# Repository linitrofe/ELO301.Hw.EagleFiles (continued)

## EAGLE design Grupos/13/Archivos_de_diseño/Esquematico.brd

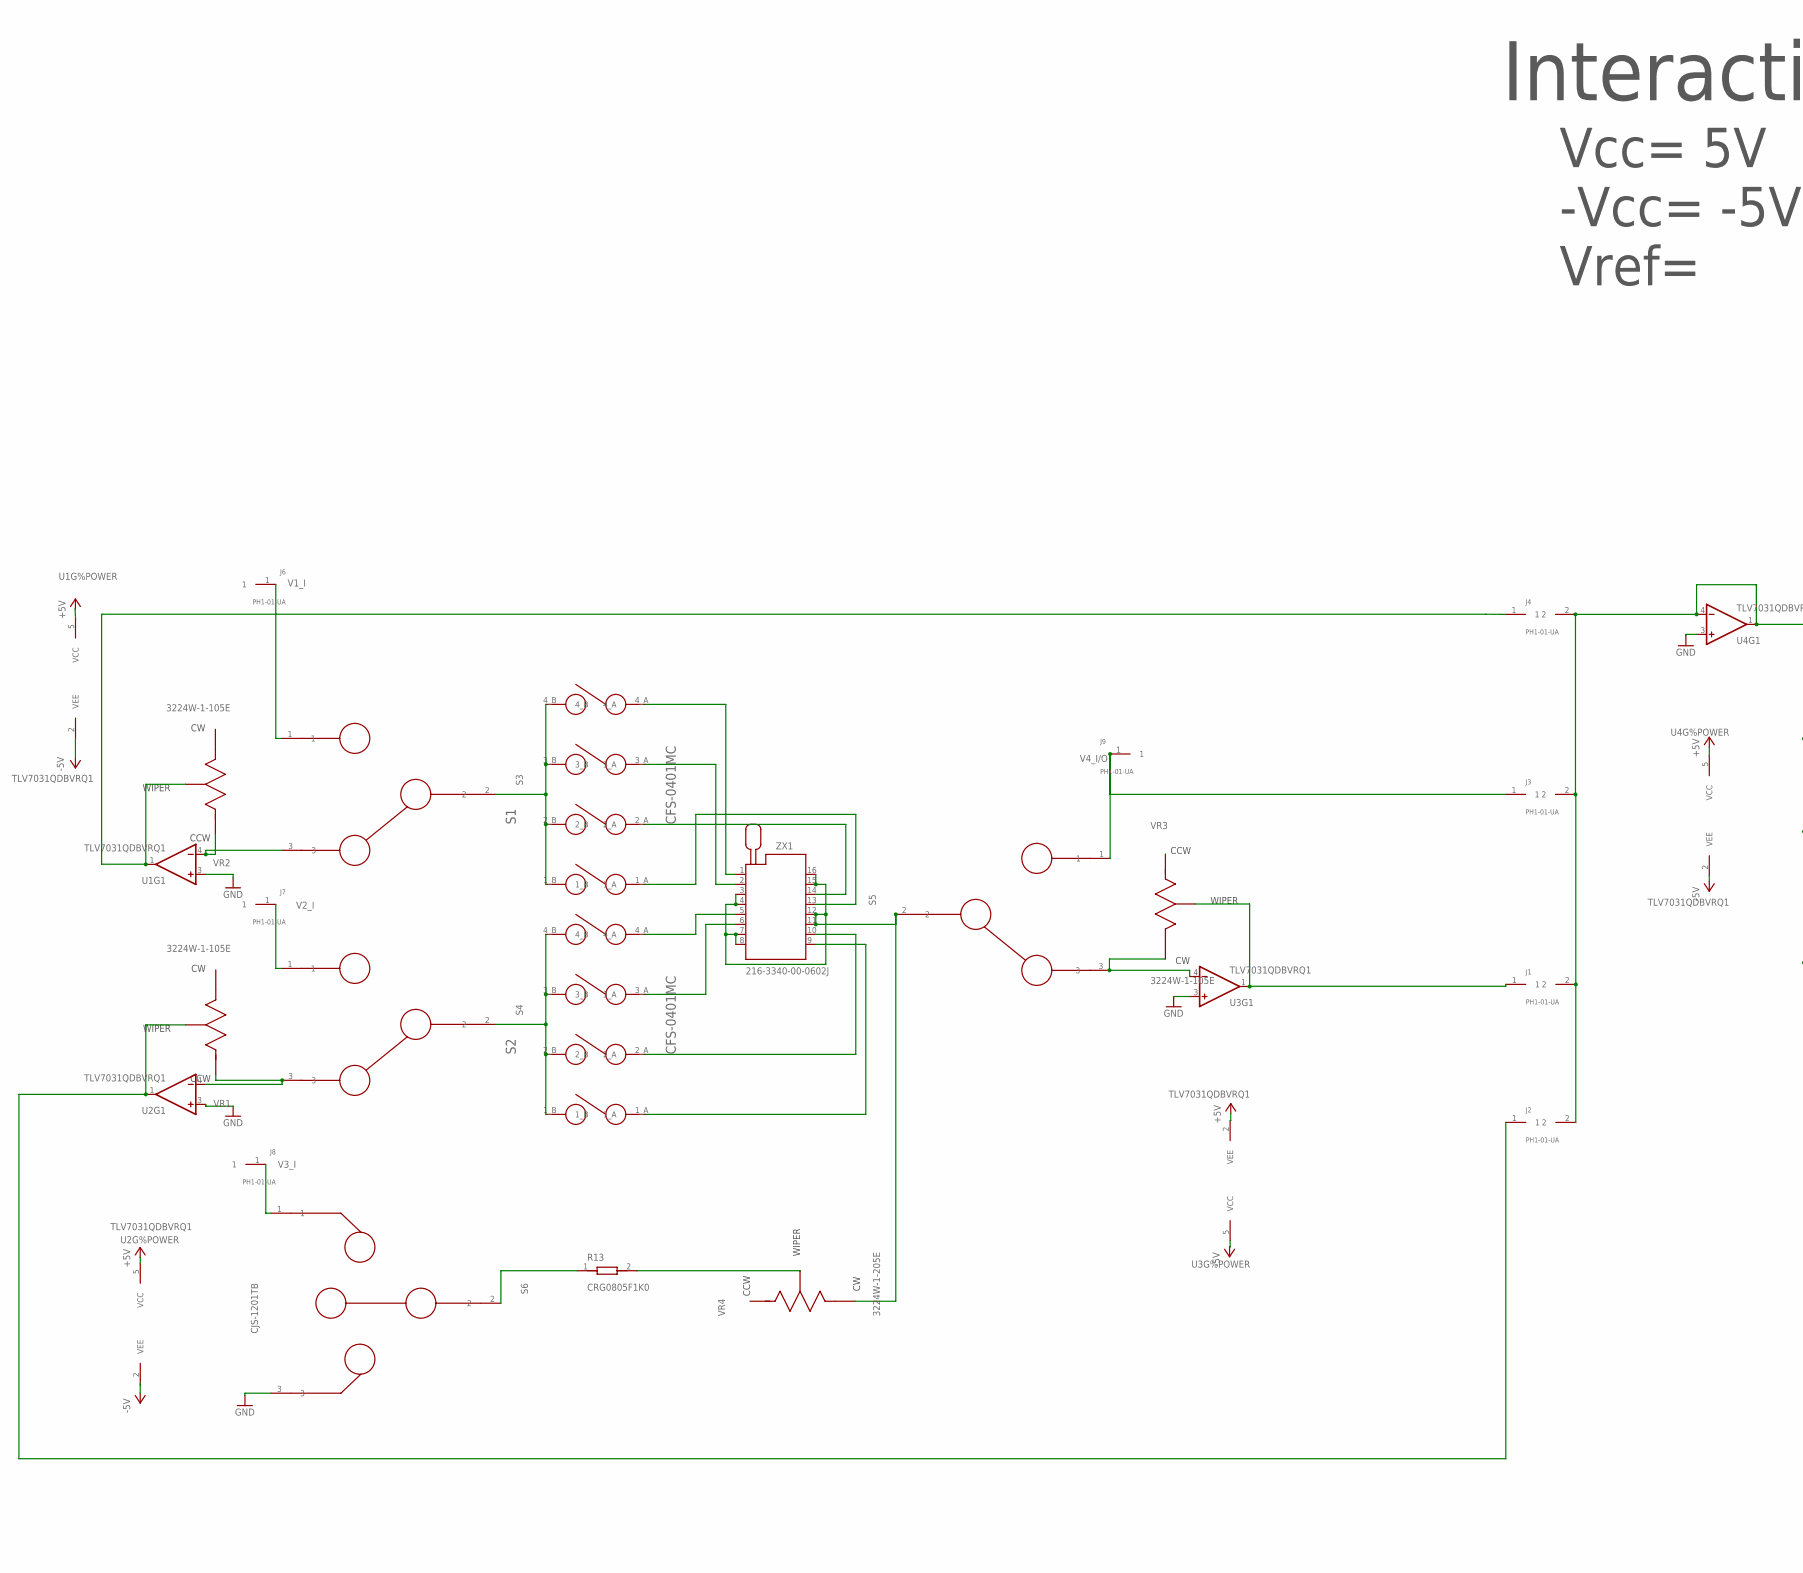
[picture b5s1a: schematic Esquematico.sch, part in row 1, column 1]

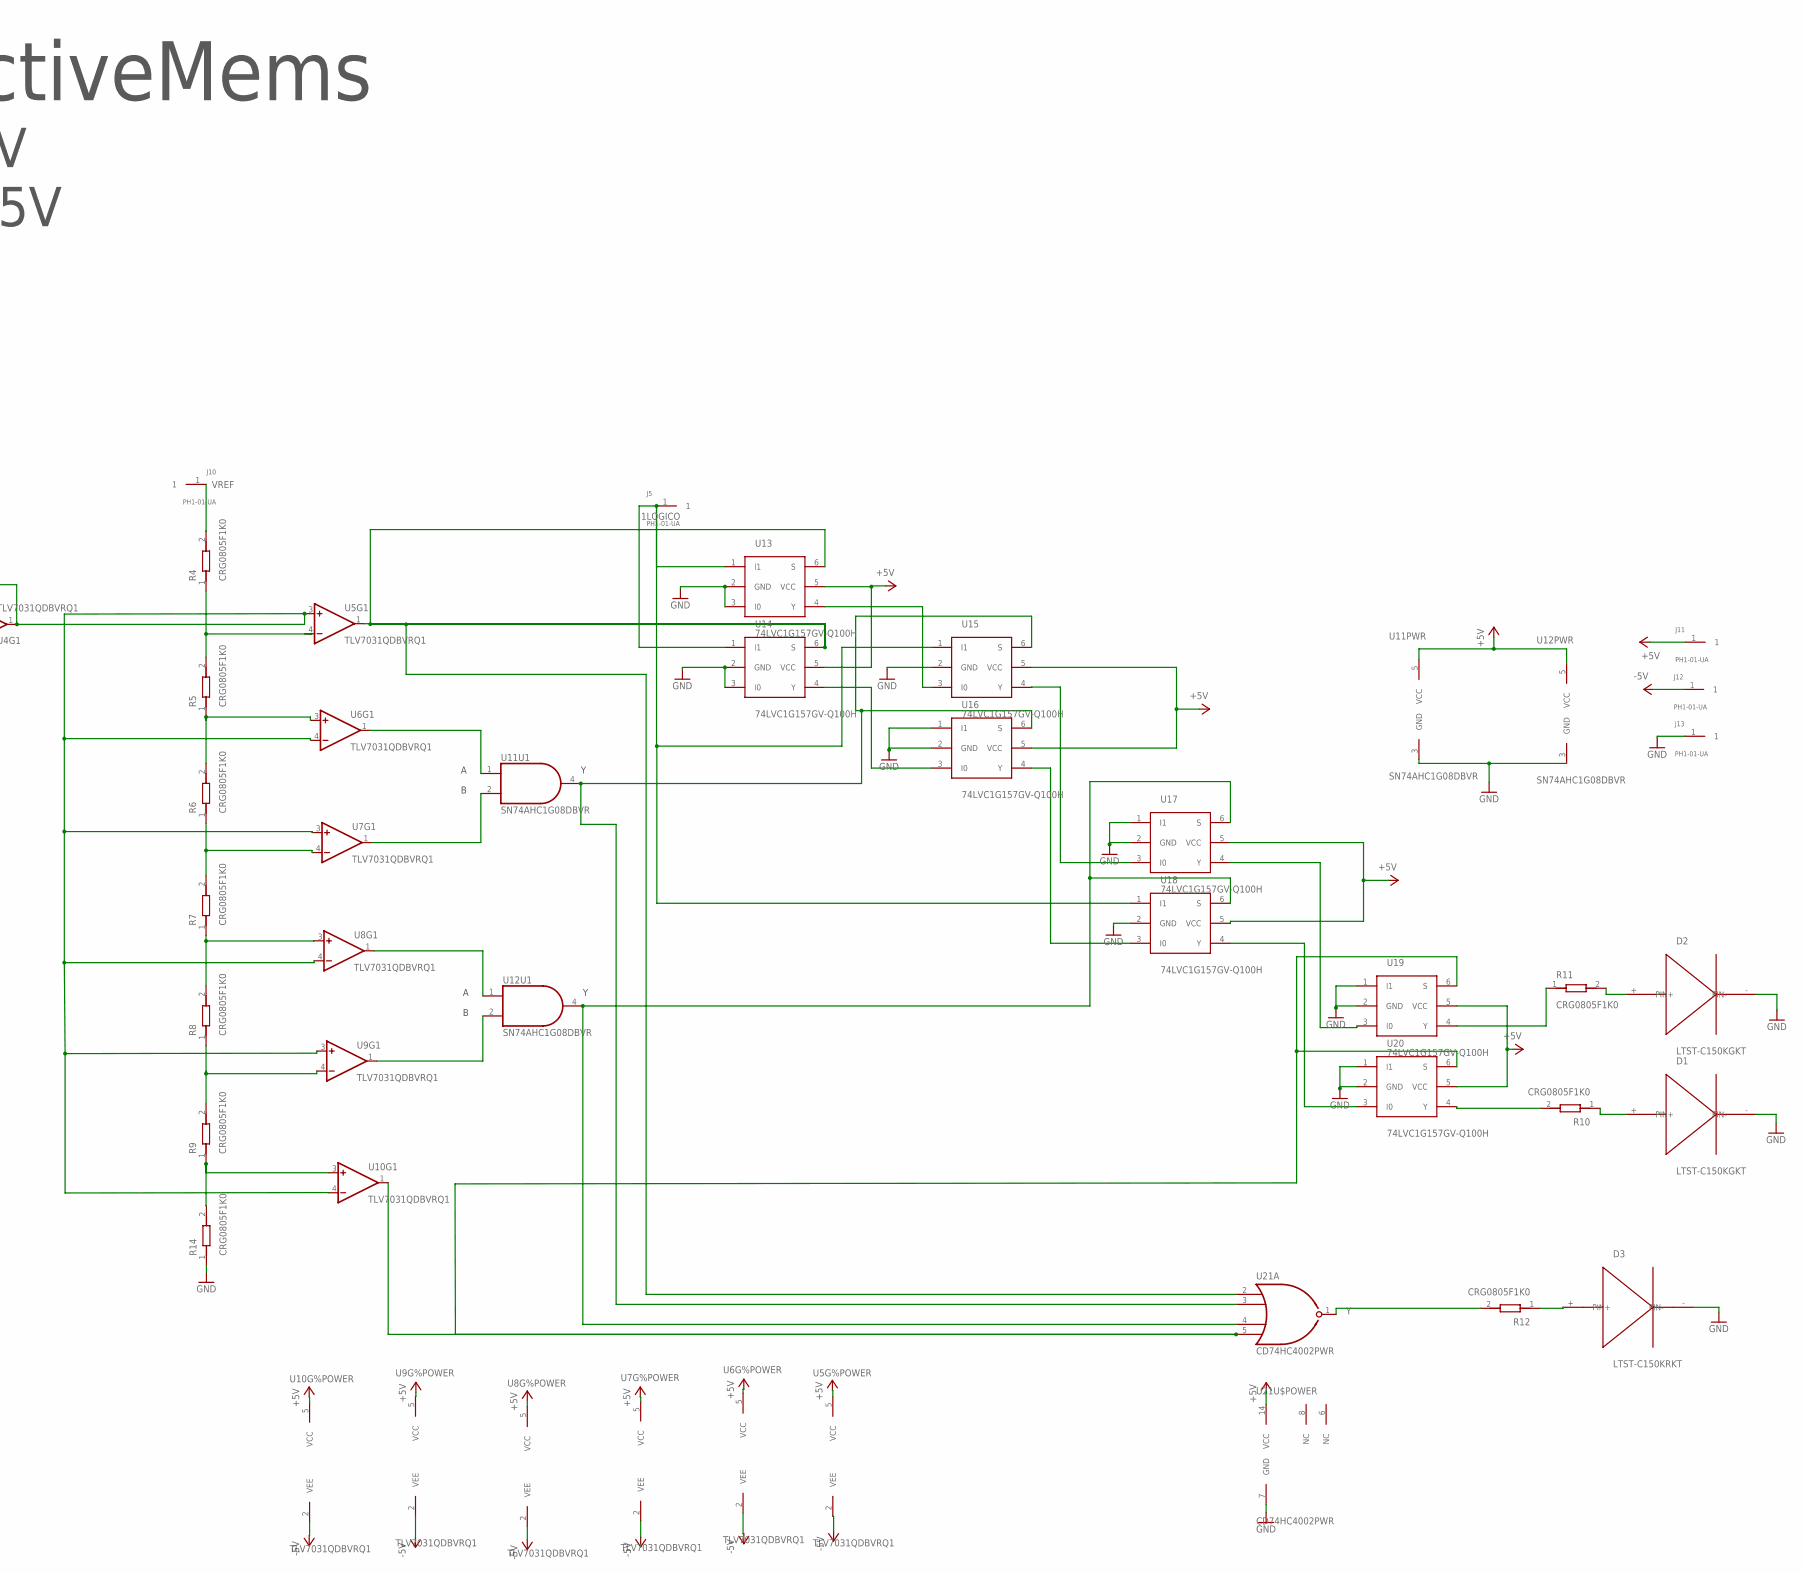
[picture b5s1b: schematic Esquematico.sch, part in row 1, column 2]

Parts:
D1, D2: LTST-C150KGKT; 1206; PARTNO LTST-C150KGKT
D3: LTST-C150KRKT; 1206; PARTNO LTST-C150KRKT
J1, J2, J3, J4, J5, J6, J7, J8, J9, J10, J11, J12, J13: PH1-01-UA; HEADER; PARTNO PH1-01-UA
R4, R5, R6, R7, R8, R9, R10, R11, R12, R13, R14: CRG0805F1K0; 0805; PARTNO CRG0805F1K0
S1, S2: CFS-0401MC; DIP_SPST-4; PARTNO CFS-0401MC
S3, S4, S5: CJS-1200TB; SPDT; PARTNO CJS-1200TB
S6: CJS-1201TB; SPDT_ON-OFF-ON; PARTNO CJS-1201TB
U1, U2, U3, U4, U5, U6, U7, U8, U9, U10: TLV7031QDBVRQ1; SOT-23; PARTNO TLV7031QDBVRQ1
U11, U12: SN74AHC1G08DBVR; SOT-23-5; PARTNO SN74AHC1G08DBVR
U13, U14, U15, U16, U17, U18, U19, U20: 74LVC1G157GV-Q100H; 6-TSOP; PARTNO 74LVC1G157GV-Q100H
U21: CD74HC4002PWR; 14-TSSOP; PARTNO CD74HC4002PWR
VR1, VR2, VR3: 3224W-1-105E; 3224W-1-205E; PARTNO 3224W-1-105E
VR4: 3224W-1-205E; PARTNO 3224W-1-205E
ZX1: 216-3340-00-0602J; PARTNO 216-3340-00-0602J

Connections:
1LOGICO: J5.1, U13.1 (I1), U14.1 (I1), U15.1 (I1), U18.1 (I1)
+5V: J11.1, U1.5 (VCC), U2.5 (VCC), U3.2 (VEE), U4.5 (VCC), U5.5 (VCC), U6.5 (VCC), U7.5 (VCC), U8.5 (VCC), U9.5 (VCC), U10.5 (VCC), U11.5 (VCC), U12.5 (VCC), U13.5 (VCC), U14.5 (VCC), U15.5 (VCC), U16.5 (VCC), U17.5 (VCC), U18.5 (VCC), U19.5 (VCC), U20.5 (VCC), U21.14 (VCC)
-5V: J12.1, U1.2 (VEE), U2.2 (VEE), U3.5 (VCC), U4.2 (VEE), U5.2 (VEE), U6.2 (VEE), U7.2 (VEE), U8.2 (VEE), U9.2 (VEE), U10.2 (VEE)
GND: D1.- (PIN-), D2.- (PIN-), D3.- (PIN-), J13.1, R14.1, S6.3, U1.3 (+IN), U2.3 (+IN), U3.3 (+IN), U4.3 (+IN), U11.3 (GND), U12.3 (GND), U13.2 (GND), U13.3 (I0), U14.2 (GND), U14.3 (I0), U15.2 (GND), U16.1 (I1), U16.2 (GND), U17.1 (I1), U17.2 (GND), U18.2 (GND), U19.1 (I1), U19.2 (GND), U20.1 (I1), U20.2 (GND), U21.7 (GND)
unnamed: S5.2, VR4.3 (CW), ZX1.3, ZX1.4, ZX1.7, ZX1.8, ZX1.11, ZX1.12, ZX1.15, ZX1.16
unnamed: S1.4_A, ZX1.1
unnamed: S1.3_A, ZX1.2
unnamed: S1.2_A, ZX1.14
unnamed: S1.1_A, ZX1.13
unnamed: R6.1, R7.2, U7.4 (-IN)
unnamed: U9.1 (OUT), U12.2 (B)
unnamed: S2.2_A, ZX1.10
unnamed: S2.1_A, ZX1.9
unnamed: S1.1_B, S1.2_B, S1.3_B, S1.4_B, S3.2
unnamed: S2.1_B, S2.2_B, S2.3_B, S2.4_B, S4.2
unnamed: S3.3, U1.4 (-IN), VR2.1 (CCW)
unnamed: S4.3, U2.4 (-IN), VR1.1 (CCW)
unnamed: S5.3, U3.4 (-IN), VR3.3 (CW)
unnamed: D2.+ (PIN+), R11.2
unnamed: D1.+ (PIN+), R10.1
unnamed: D3.+ (PIN+), R12.1
unnamed: J1.2, J2.2, J3.2, J4.2, U4.1 (OUT), U4.4 (-IN), U5.3 (+IN), U6.4 (-IN), U7.3 (+IN), U8.4 (-IN), U9.3 (+IN), U10.4 (-IN)
unnamed: R13.1, S6.2
unnamed: U8.1 (OUT), U12.1 (A)
unnamed: U7.1 (OUT), U11.2 (B)
unnamed: U6.1 (OUT), U11.1 (A)
unnamed: R13.2, VR4.2 (WIPER)
unnamed: S2.4_A, ZX1.5
unnamed: R4.1, R5.2, U5.4 (-IN)
unnamed: S2.3_A, ZX1.6
unnamed: R5.1, R6.2, U6.3 (+IN)
unnamed: R9.1, R14.2, U10.3 (+IN)
unnamed: R7.1, R8.2, U8.3 (+IN)
unnamed: R8.1, R9.2, U9.4 (-IN)
unnamed: U5.1 (OUT), U13.6 (S), U14.6 (S), U21.2 (A)
unnamed: U11.4 (Y), U15.6 (S), U16.6 (S), U21.3 (B)
unnamed: U15.4 (Y), U17.3 (I0)
unnamed: U14.4 (Y), U16.3 (I0)
unnamed: U13.4 (Y), U15.3 (I0)
unnamed: U16.4 (Y), U18.3 (I0)
unnamed: U12.4 (Y), U17.6 (S), U18.6 (S), U21.4 (C)
unnamed: U17.4 (Y), U19.3 (I0)
unnamed: U18.4 (Y), U20.3 (I0)
unnamed: R10.2, U20.4 (Y)
unnamed: R11.1, U19.4 (Y)
unnamed: U10.1 (OUT), U19.6 (S), U20.6 (S), U21.5 (D)
unnamed: R12.2, U21.1 (Y)
V1_I: J6.1, S3.1
V1_O: J4.1, U1.1 (OUT), VR2.2 (WIPER)
V2_I: J7.1, S4.1
V2_O: J2.1, U2.1 (OUT), VR1.2 (WIPER)
V3_I: J8.1, S6.1
V3_O: J1.1, U3.1 (OUT), VR3.2 (WIPER)
V4_I/O: J3.1, J9.1, S5.1
VREF: J10.1, R4.2

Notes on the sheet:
InteractiveMems
Vcc= 5V -Vcc= -5V Vref=

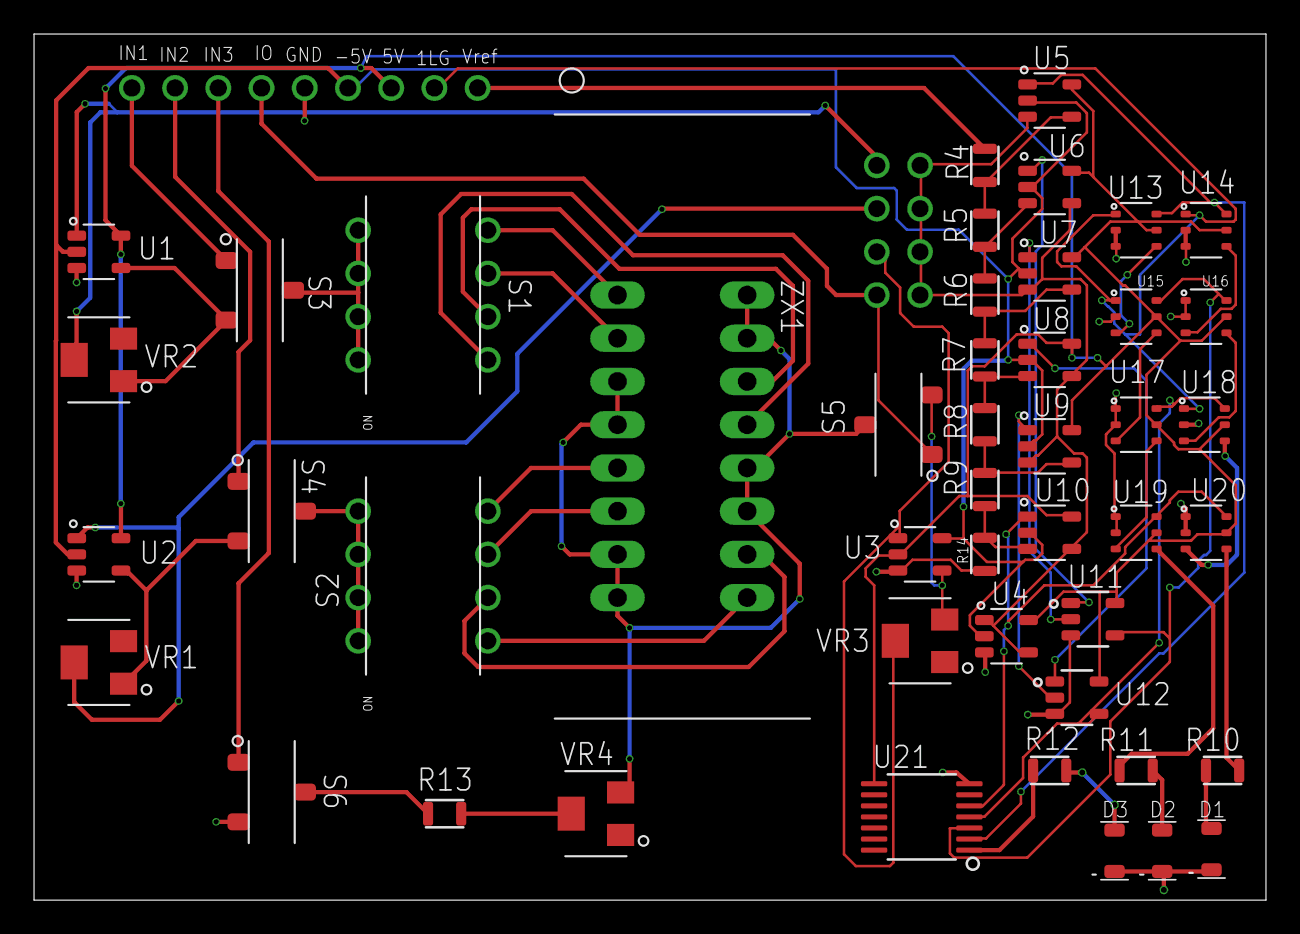
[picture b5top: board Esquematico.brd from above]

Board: 2 copper layers, 72.4 x 50.9 mm, 59 parts (0 on the bottom side), 55 nets.

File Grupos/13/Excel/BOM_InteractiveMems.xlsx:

Qty | Value | Device | Package | Parts | Description | PARTNO | Column1
1 | 216-3340-00-0602J | 216-3340-00-0602J | 216-3340-00-0602J | ZX1 | Zero Insertion Force Socked | 216-3340-00-0602J
3 | 3224W-1-105E | 3224W-1-205E | 3224W-1-205E | VR1, VR2, VR3 |  | 3224W-1-105E
1 | 3224W-1-205E | 3224W-1-205E | 3224W-1-205E | VR4 |  | 3224W-1-205E
8 | 74LVC1G157GV-Q100H | 74LVC1G157GV-Q100H | 6-TSOP | U13, U14, U15, U16, U17, U18, U19, U20 |  | 74LVC1G157GV-Q100H
1 | CD74HC4002PWR | CD74HC4002PWR | 14-TSSOP | U21 |  | CD74HC4002PWR
2 | CFS-0401MC | CFS-0401MC | DIP_SPST-4 | S1, S2 |  | CFS-0401MC
3 | CJS-1200TB | CJS-1200B | SPDT | S3, S4, S5 |  | CJS-1200TB
1 | CJS-1201TB | CJS-1201TB | SPDT_ON-OFF-ON | S6 |  | CJS-1201TB
1 | CRG0805F1K0 | CRG0805F1K0 | 0805 | R13 |  | CRG0805F1K0
10 | CRG0805F1K0 | CRG0805F1K0 | 0805 | R4, R5, R6, R7, R8, R9, R10, R11, R12, R14 |  | CRG0805F1K0
2 | LTST-C150KGKT | LTST-C150KRKT | 1206 | D1, D2 |  | LTST-C150KGKT
1 | LTST-C150KRKT | LTST-C150KRKT | 1206 | D3 |  | LTST-C150KRKT
4 | PH1-01-UA | (2X)PH1-01-UA | HEADER | J1, J2, J3, J4 |  | PH1-01-UA
6 | PH1-01-UA | PH1-01-UA | HEADER | J5, J6, J7, J8, J9, J10 |  | PH1-01-UA
3 | PH1-01-UA | PH1-01-UA | HEADER | J11, J12, J13 |  | PH1-01-UA
2 | SN74AHC1G08DBVR | SN74AHC1G08DBVR | SOT-23-5 | U11, U12 |  | SN74AHC1G08DBVR
10 | TLV7031QDBVRQ1 | TLV7031QDBVRQ1 | SOT-23 | U1, U2, U3, U4, U5, U6, U7, U8, U9, U10 |  | TLV7031QDBVRQ1

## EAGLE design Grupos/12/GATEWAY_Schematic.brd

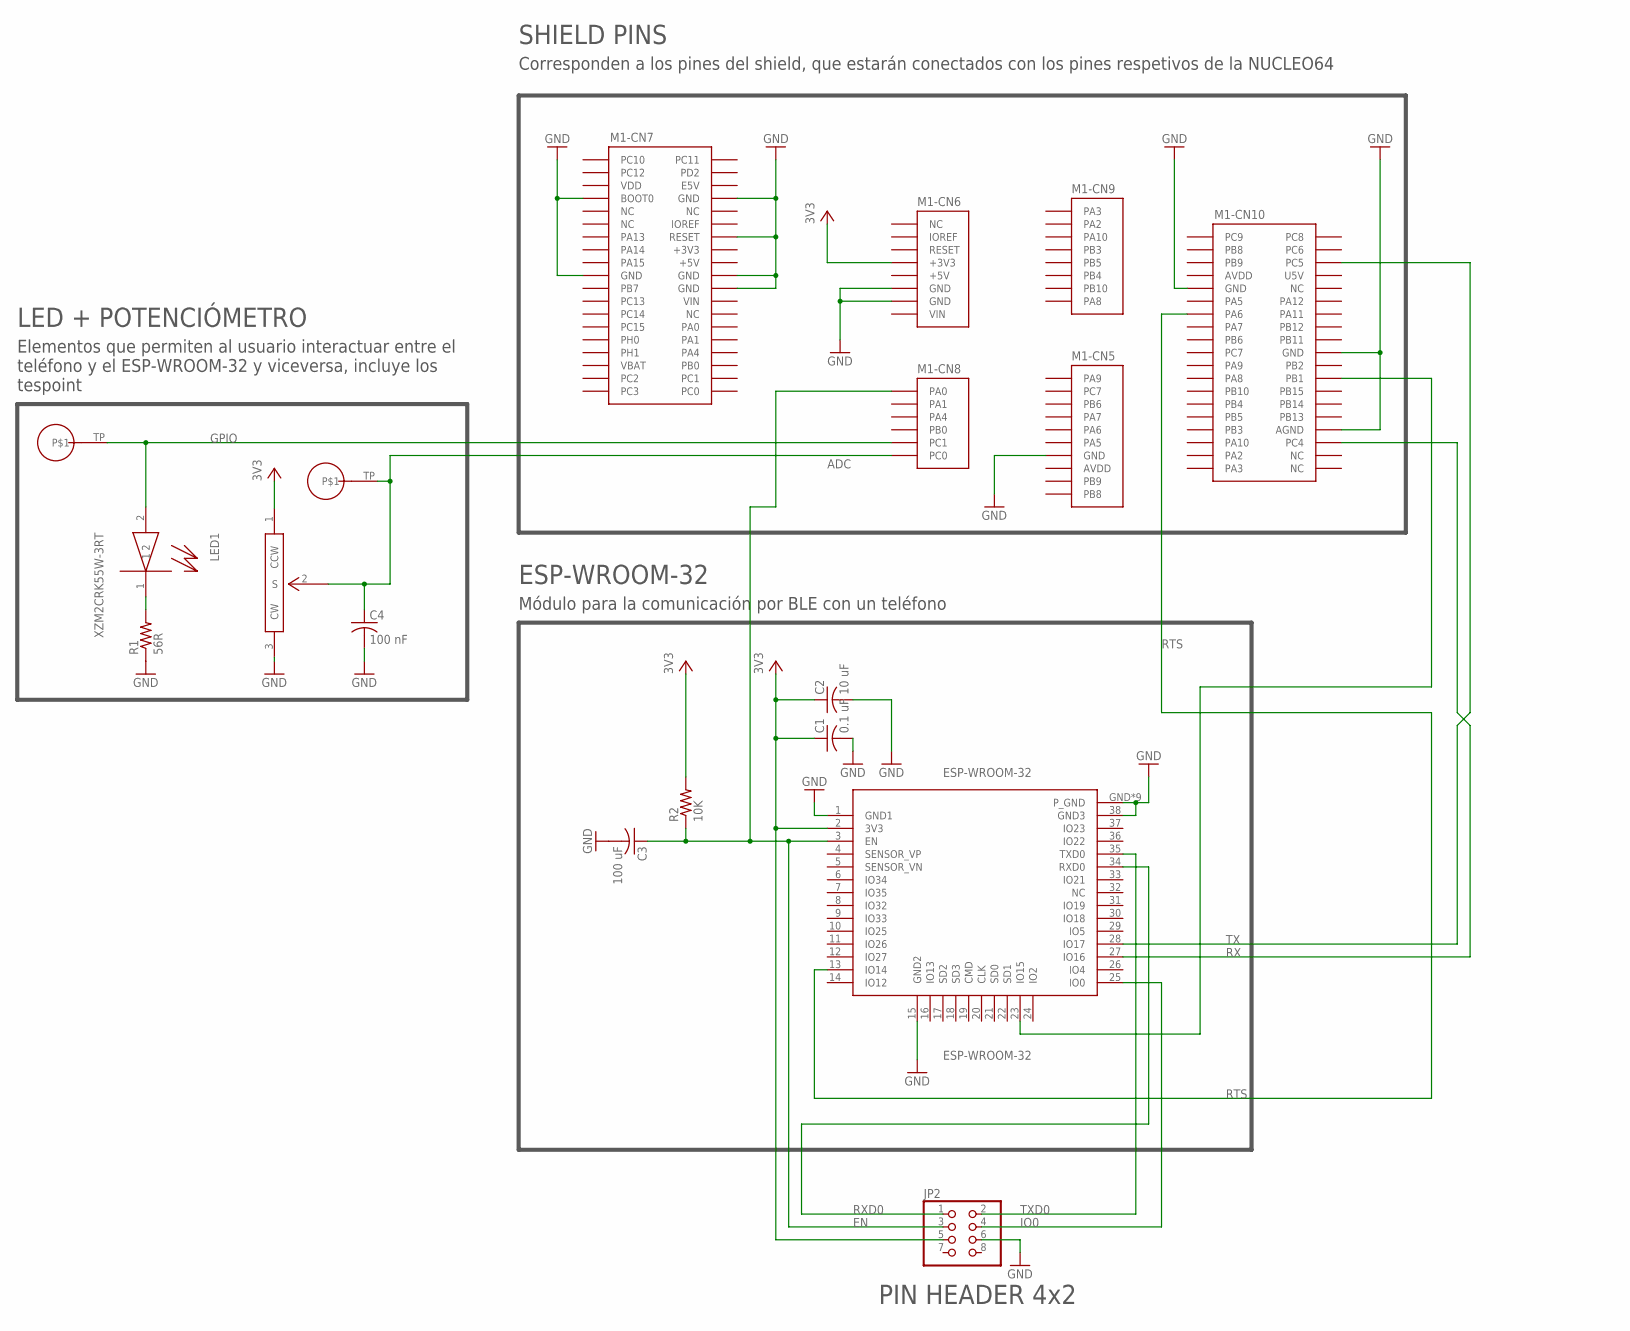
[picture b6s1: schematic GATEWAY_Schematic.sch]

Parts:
C1: 0.1 uF; C0805; PARTNO GCM21BR72A104KA37L
C2: 10 uF; C0805; PARTNO GRM21BR61C106KE15L
C3: 100 uF; C0805; PARTNO GRM21BR60J107ME15L
C4: 100 nF; C0805; PARTNO GCM21BR72A104KA37L
ESP-WROOM-32: ESP-WROOM-32; PARTNO ESP-WROOM-32
JP2: PINHD-2X4; 2X04; PARTNO 220-1-08-003
LED1: XZM2CRK55W-3RT; CHIPLED; PARTNO XZM2CRK55W-3RT
M1: NUCLEO-L452RE; NUCLEO-64; PARTNO NUCLEO-L452RE
POT1: 10K; P160KN-0QD15B10K; PARTNO P160KN-0QD15B10K
R1: 56R; R0805; PARTNO RC0805JR-0756RL
R2: 10K; R0805; PARTNO RC0805FR-0710KL
TP_LED: TP
TP_POT: TP

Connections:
+3V3: M1.CN7-16 (+3V3)
+5V: M1.CN6-5 (+5V), M1.CN7-18 (+5V)
ADC: C4.1, M1.CN8-6 (PC0), POT1.2 (S), TP_POT.TP
AVDD: M1.CN5-8 (AVDD), M1.CN10-7 (AVDD)
CTS: ESP-WROOM-32.23 (IO15), M1.CN10-24 (PB1)
EN: C3.1, ESP-WROOM-32.3 (EN), JP2.3, M1.CN8-1 (PA0), R2.1
GND: C1.2, C2.2, C3.2, C4.2, ESP-WROOM-32.1 (GND1), ESP-WROOM-32.15 (GND2), ESP-WROOM-32.38 (GND3), ESP-WROOM-32.GND (P_GND), ESP-WROOM-32.GND1 (P_GND), ESP-WROOM-32.GND2 (P_GND), ESP-WROOM-32.GND3 (P_GND), ESP-WROOM-32.GND4 (P_GND), ESP-WROOM-32.GND5 (P_GND), ESP-WROOM-32.GND6 (P_GND), ESP-WROOM-32.GND7 (P_GND), ESP-WROOM-32.GND8 (P_GND), JP2.6, M1.CN5-7 (GND), M1.CN6-6 (GND), M1.CN6-7 (GND), M1.CN7-7 (BOOT0), M1.CN7-8 (GND), M1.CN7-14 (RESET), M1.CN7-19 (GND), M1.CN7-20 (GND), M1.CN7-22 (GND), M1.CN10-9 (GND), M1.CN10-20 (GND), M1.CN10-32 (AGND), POT1.3 (CW), R1.1
GPIO: LED1.2, M1.CN8-5 (PC1), TP_LED.TP
IO0: ESP-WROOM-32.25 (IO0), JP2.4
IOREF: M1.CN6-2 (IOREF)
unnamed: LED1.1, R1.2
RTS: ESP-WROOM-32.13 (IO14), M1.CN10-13 (PA6)
RX: ESP-WROOM-32.27 (IO16), M1.CN10-34 (PC4)
RXD0: ESP-WROOM-32.34 (RXD0), JP2.1
TX: ESP-WROOM-32.28 (IO17), M1.CN10-6 (PC5)
TXD0: ESP-WROOM-32.35 (TXD0), JP2.2
U5V: M1.CN10-8 (U5V)
VBAT: M1.CN7-33 (VBAT)
VCC: C1.1, C2.1, ESP-WROOM-32.2 (3V3), JP2.5, M1.CN6-4 (+3V3), POT1.1 (CCW), R2.2
VDD: M1.CN7-5 (VDD)
VIN: M1.CN6-8 (VIN), M1.CN7-24 (VIN)

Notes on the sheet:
LED + POTENCIÓMETRO
SHIELD PINS
ESP-WROOM-32
PIN HEADER 4x2
Corresponden a los pines del shield, que estarán conectados con los pines respetivos de la NUCLEO64
Elementos que permiten al usuario interactuar entre el teléfono y el ESP-WROOM-32 y viceversa, incluye los tespoint
Módulo para la comunicación por BLE con un teléfono

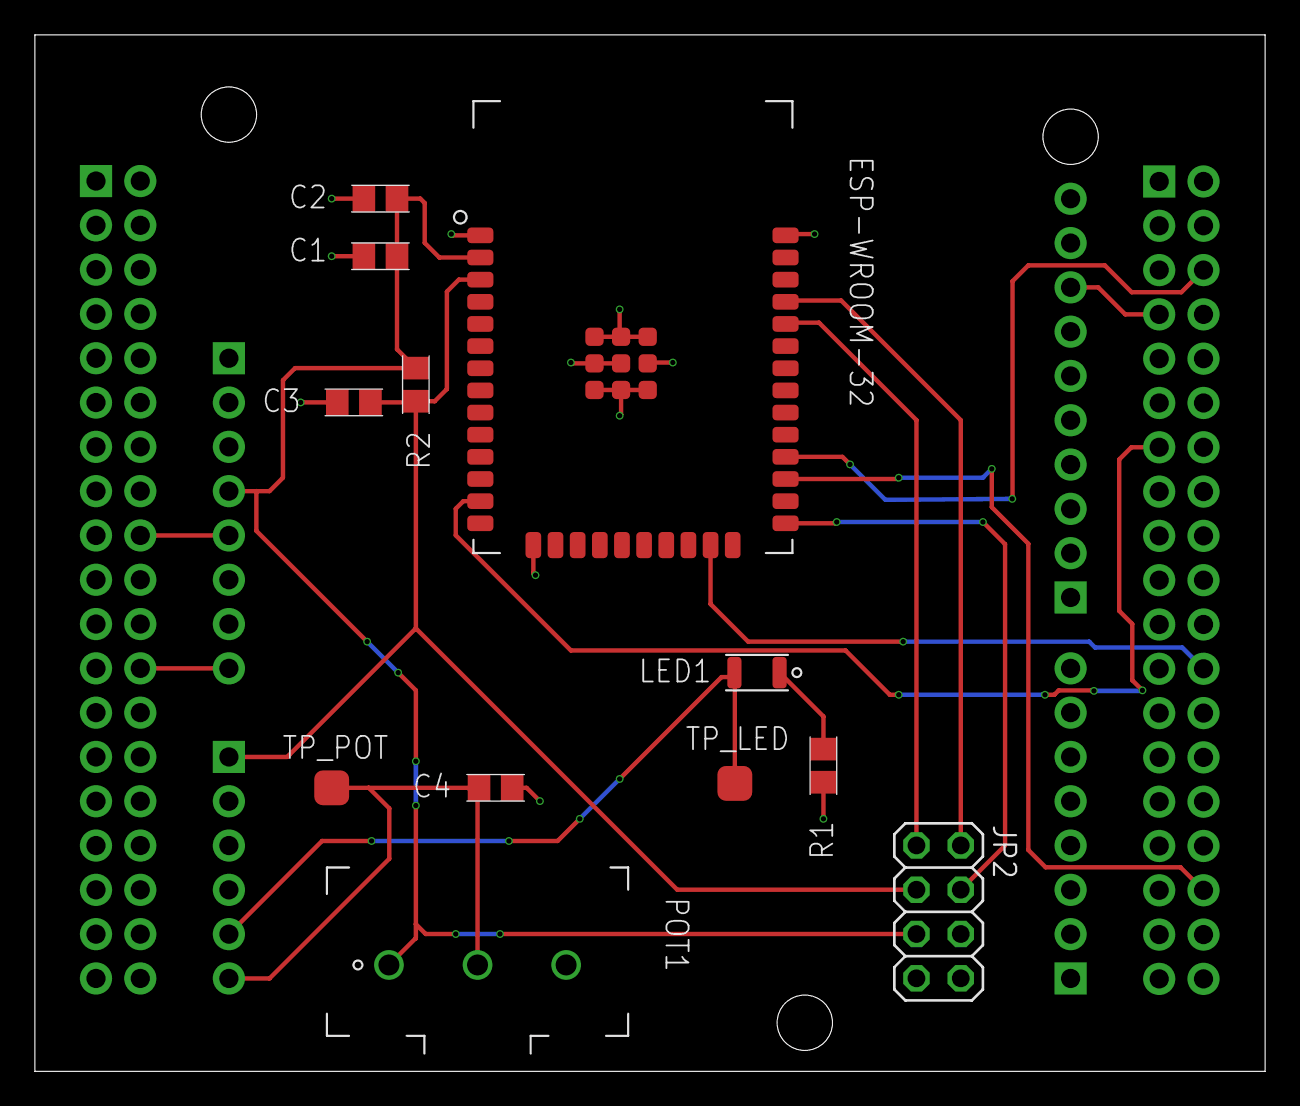
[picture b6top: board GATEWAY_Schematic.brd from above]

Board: 2 copper layers, 70.5 x 59.4 mm, 13 parts (0 on the bottom side), 16 nets.

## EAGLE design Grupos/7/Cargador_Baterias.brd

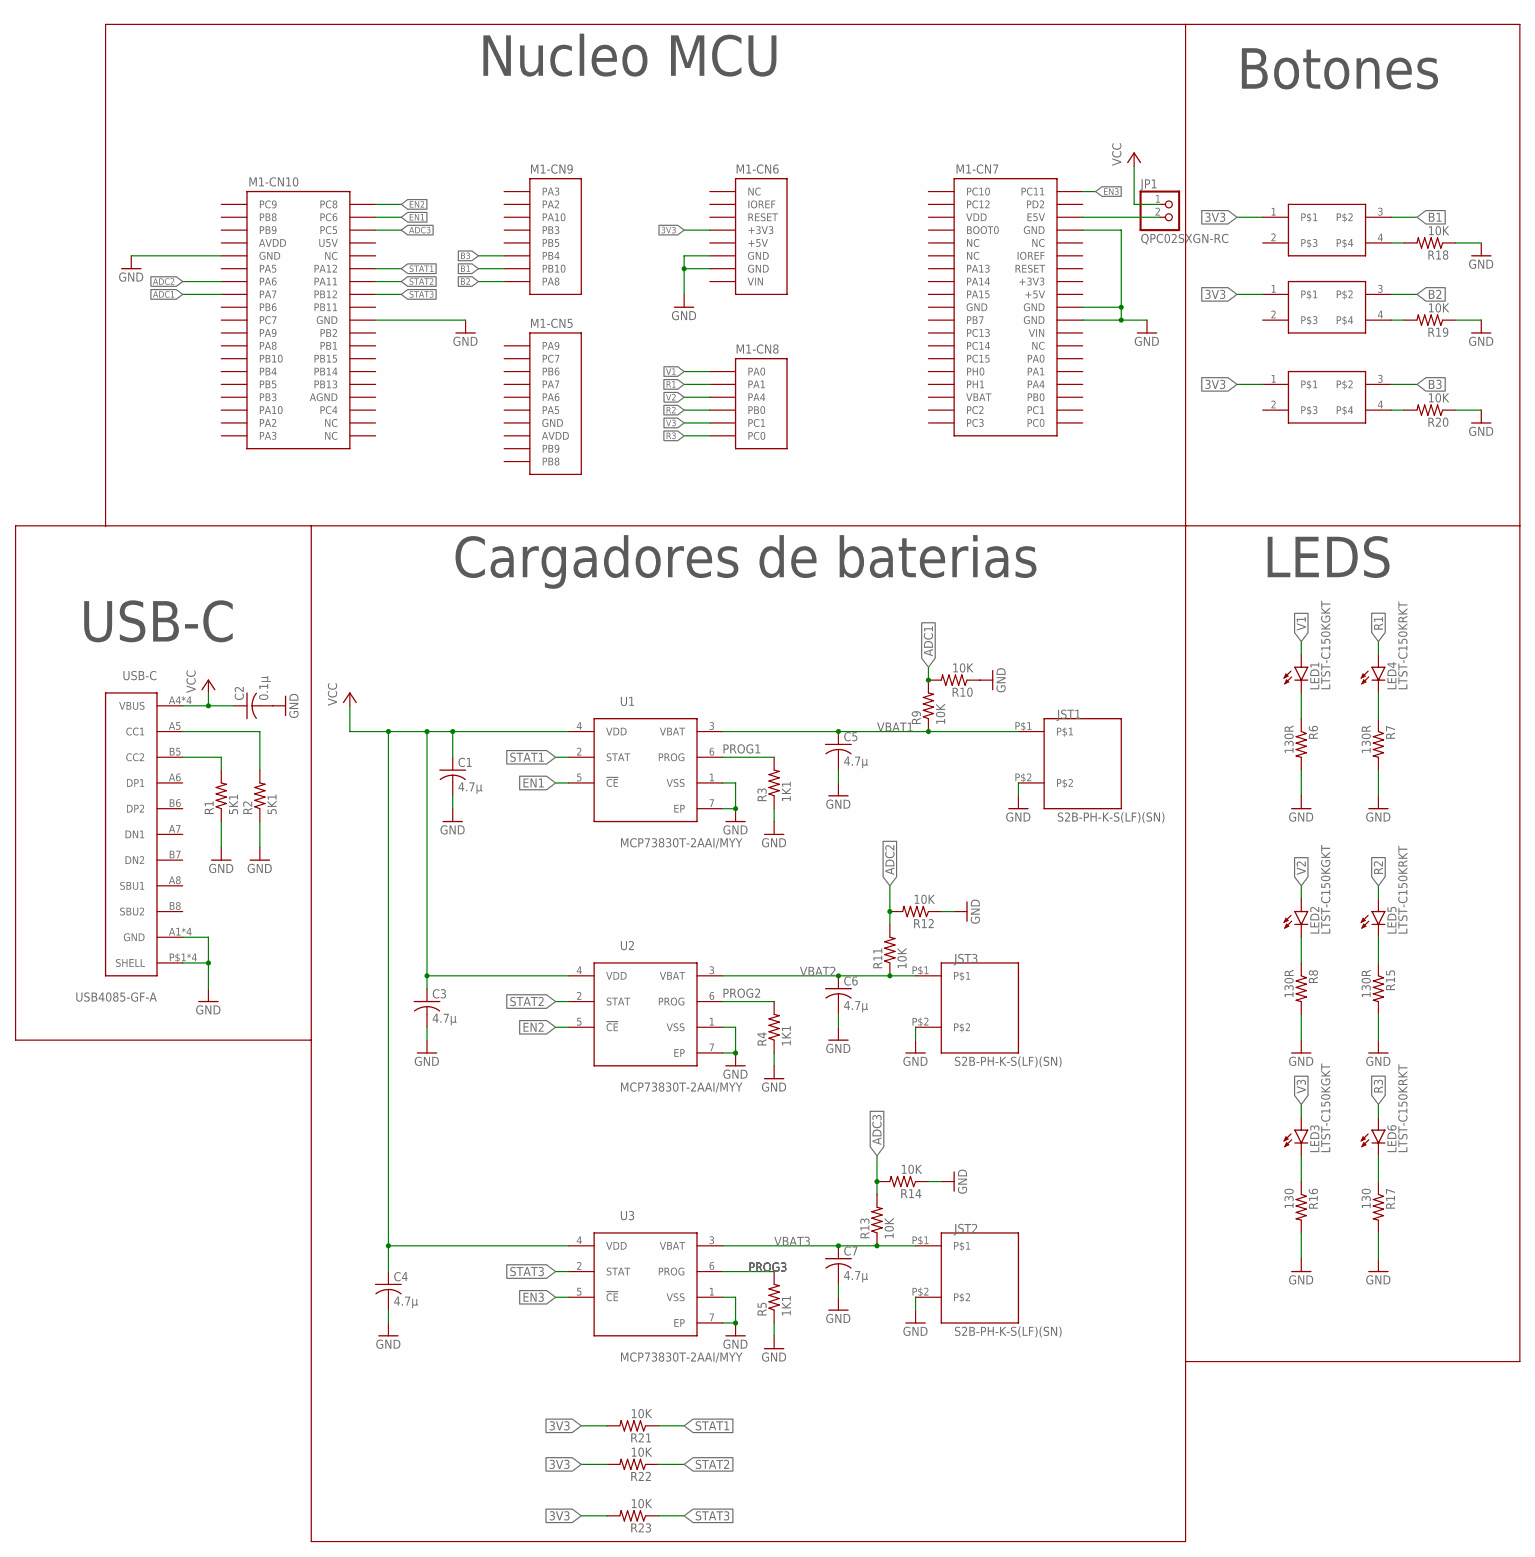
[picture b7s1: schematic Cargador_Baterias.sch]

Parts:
BOTON1, BOTON2, BOTON3: PTS645SM43SMTR92 LFS; PTS645SM43SMTR92LFS; PARTNO PTS645SM43SMTR92 LFS
C1, C3, C4, C5, C6, C7: 4.7µ; C0805; PARTNO GRM21BR71C475KE51L
C2: 0.1µ; C0805; PARTNO GCJ21BL81H104KA01L
JP1: QPC02SXGN-RC; 1X02; PARTNO QPC02SXGN-RC
JST1, JST2, JST3: S2B-PH-K-S(LF)(SN); BULK; PARTNO S2B-PH-K-S(LF)(SN)
LED1, LED2, LED3: LTST-C150KGKT; 1206; PARTNO LTST-C150KGKT
LED4, LED5, LED6: LTST-C150KRKT; 1206; PARTNO LTST-C150KRKT
M1: NUCLEO-L452RE; NUCLEO-64; PARTNO NUCLEO-L452RE
R1, R2: 5K1; R0805; PARTNO RC0805FR-075K1L
R3, R4, R5: 1K1; R0805; PARTNO RC0805FR-071K1L
R6, R7, R8, R15: 130R; R0805; PARTNO RC0805FR-07130RL
R9, R10, R11, R12, R13, R14, R18, R19, R20, R21, R22, R23: 10K; R0805; PARTNO RC0805JR-1310KL
R16, R17: 130; R0805; PARTNO RC0805FR-07130RL
U1, U2, U3: MCP73830T-2AAI/MYY; 6-TDFN(2X2); PARTNO MCP73830T-2AAI/MYY
USB-C: USB4085-GF-A; PARTNO USB4085-GF-A

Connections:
3V3: BOTON1.1, BOTON2.1, BOTON3.1, M1.CN6-4 (+3V3), R21.2, R22.2, R23.2
+3V3: M1.CN7-16 (+3V3)
+5V: M1.CN6-5 (+5V), M1.CN7-18 (+5V)
ADC1: M1.CN10-15 (PA7), R9.2, R10.2
ADC2: M1.CN10-13 (PA6), R11.2, R12.2
ADC3: M1.CN10-6 (PC5), R13.2, R14.2
AGND: M1.CN10-32 (AGND)
AVDD: M1.CN5-8 (AVDD), M1.CN10-7 (AVDD)
B1: BOTON1.3, M1.CN9-7 (PB10)
B2: BOTON2.3, M1.CN9-8 (PA8)
B3: BOTON3.3, M1.CN9-6 (PB4)
EN1: M1.CN10-4 (PC6), U1.5 (!CE)
EN2: M1.CN10-2 (PC8), U2.5 (!CE)
EN3: M1.CN7-2 (PC11), U3.5 (!CE)
GND: C1.2, C2.2, C3.2, C4.2, C5.2, C6.2, C7.2, JST1.P$2, JST2.P$2, JST3.P$2, M1.CN5-7 (GND), M1.CN6-6 (GND), M1.CN6-7 (GND), M1.CN7-8 (GND), M1.CN7-19 (GND), M1.CN7-20 (GND), M1.CN7-22 (GND), M1.CN10-9 (GND), M1.CN10-20 (GND), R1.1, R2.1, R3.1, R4.1, R5.1, R6.2, R7.2, R8.2, R10.1, R12.1, R14.1, R15.2, R16.2, R17.2, R18.1, R19.1, R20.1, U1.1 (VSS), U1.7 (EP), U2.1 (VSS), U2.7 (EP), U3.1 (VSS), U3.7 (EP), USB-C.A1 (GND), USB-C.A12 (GND), USB-C.B1 (GND), USB-C.B12 (GND), USB-C.P$1 (SHELL), USB-C.P$2 (SHELL), USB-C.P$3 (SHELL), USB-C.P$4 (SHELL)
IOREF: M1.CN6-2 (IOREF)
unnamed: R1.2, USB-C.B5 (CC2)
unnamed: R2.2, USB-C.A5 (CC1)
unnamed: LED1.C, R6.1
unnamed: LED4.C, R7.1
unnamed: LED2.C, R8.1
unnamed: LED5.C, R15.1
unnamed: JP1.2, M1.CN7-6 (E5V)
unnamed: LED3.C, R16.1
unnamed: LED6.C, R17.1
unnamed: BOTON1.4, R18.2
unnamed: BOTON2.4, R19.2
unnamed: BOTON3.4, R20.2
PROG1: R3.2, U1.6 (PROG)
PROG2: R4.2, U2.6 (PROG)
PROG3: R5.2, U3.6 (PROG)
R1: LED4.A, M1.CN8-2 (PA1)
R2: LED5.A, M1.CN8-4 (PB0)
R3: LED6.A, M1.CN8-6 (PC0)
STAT1: M1.CN10-12 (PA12), R21.1, U1.2 (STAT)
STAT2: M1.CN10-14 (PA11), R22.1, U2.2 (STAT)
STAT3: M1.CN10-16 (PB12), R23.1, U3.2 (STAT)
U5V: M1.CN10-8 (U5V)
V1: LED1.A, M1.CN8-1 (PA0)
V2: LED2.A, M1.CN8-3 (PA4)
V3: LED3.A, M1.CN8-5 (PC1)
VBAT: M1.CN7-33 (VBAT)
VBAT1: C5.1, JST1.P$1, R9.1, U1.3 (VBAT)
VBAT2: C6.1, JST3.P$1, R11.1, U2.3 (VBAT)
VBAT3: C7.1, JST2.P$1, R13.1, U3.3 (VBAT)
VCC: C1.1, C2.1, C3.1, C4.1, JP1.1, U1.4 (VDD), U2.4 (VDD), U3.4 (VDD), USB-C.A4 (VBUS), USB-C.A9 (VBUS), USB-C.B4 (VBUS), USB-C.B9 (VBUS)
VDD: M1.CN7-5 (VDD)
VIN: M1.CN6-8 (VIN), M1.CN7-24 (VIN)

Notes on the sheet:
USB-C
Cargadores de baterias
Nucleo MCU
Botones
LEDS

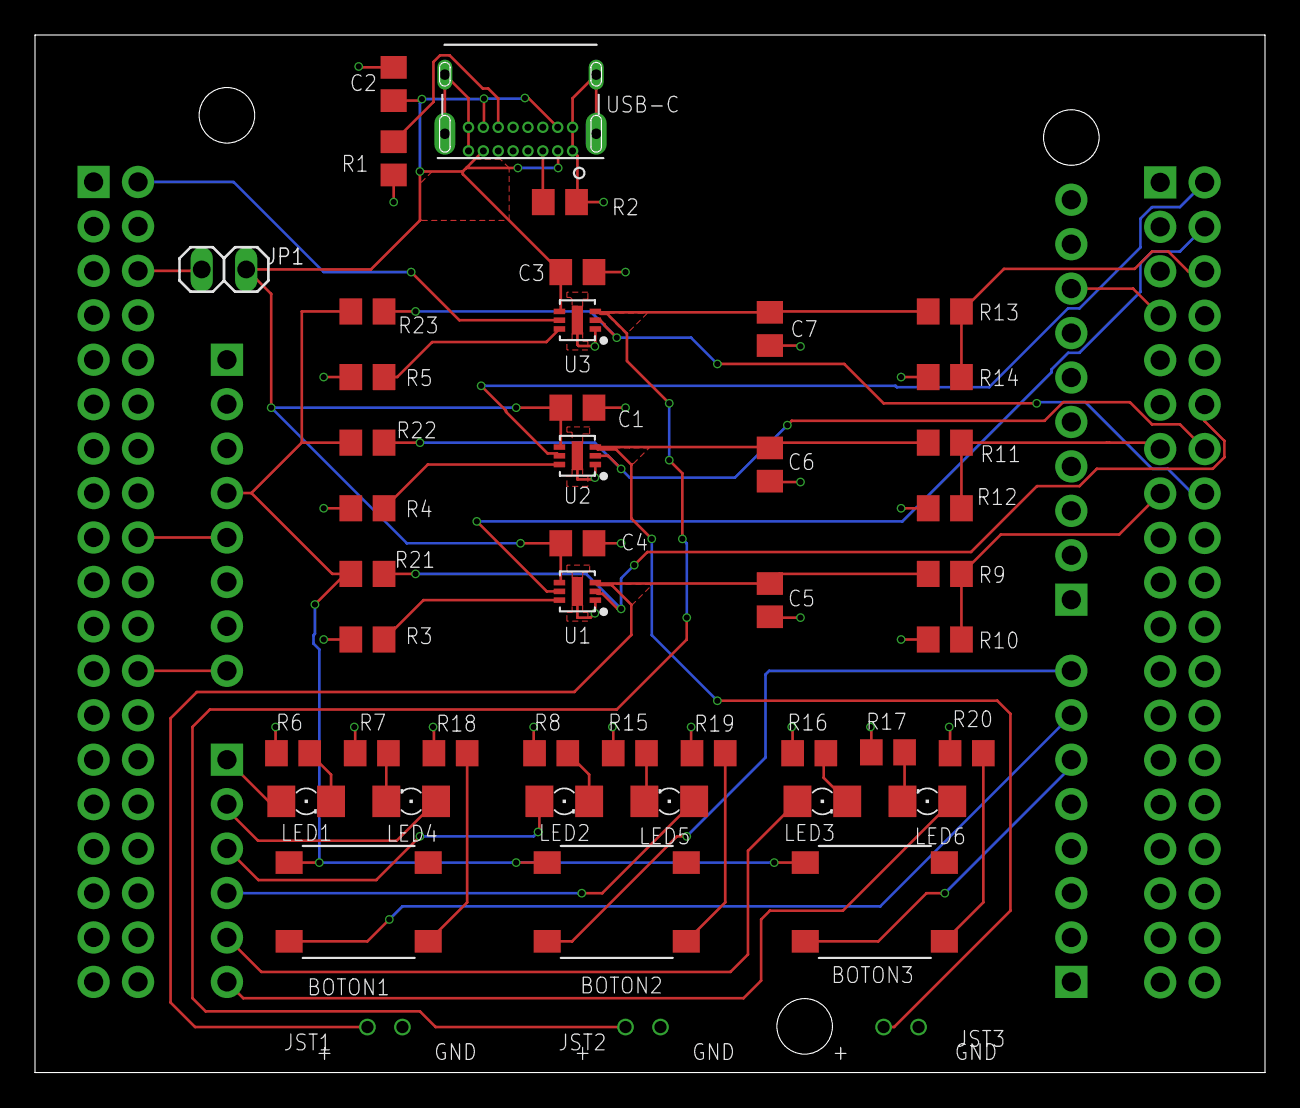
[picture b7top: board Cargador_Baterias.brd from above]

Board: 2 copper layers, 70.3 x 59.3 mm, 48 parts (0 on the bottom side), 42 nets.
